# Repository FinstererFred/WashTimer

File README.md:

# WashTimer

Timer for washing machine. 

Features: 

- Set time when washing machine starts
- Activate / Deactivate timer
- Set clocktime via menu
- Reads active wash-program
- Display remaining washingtime for active wash-program

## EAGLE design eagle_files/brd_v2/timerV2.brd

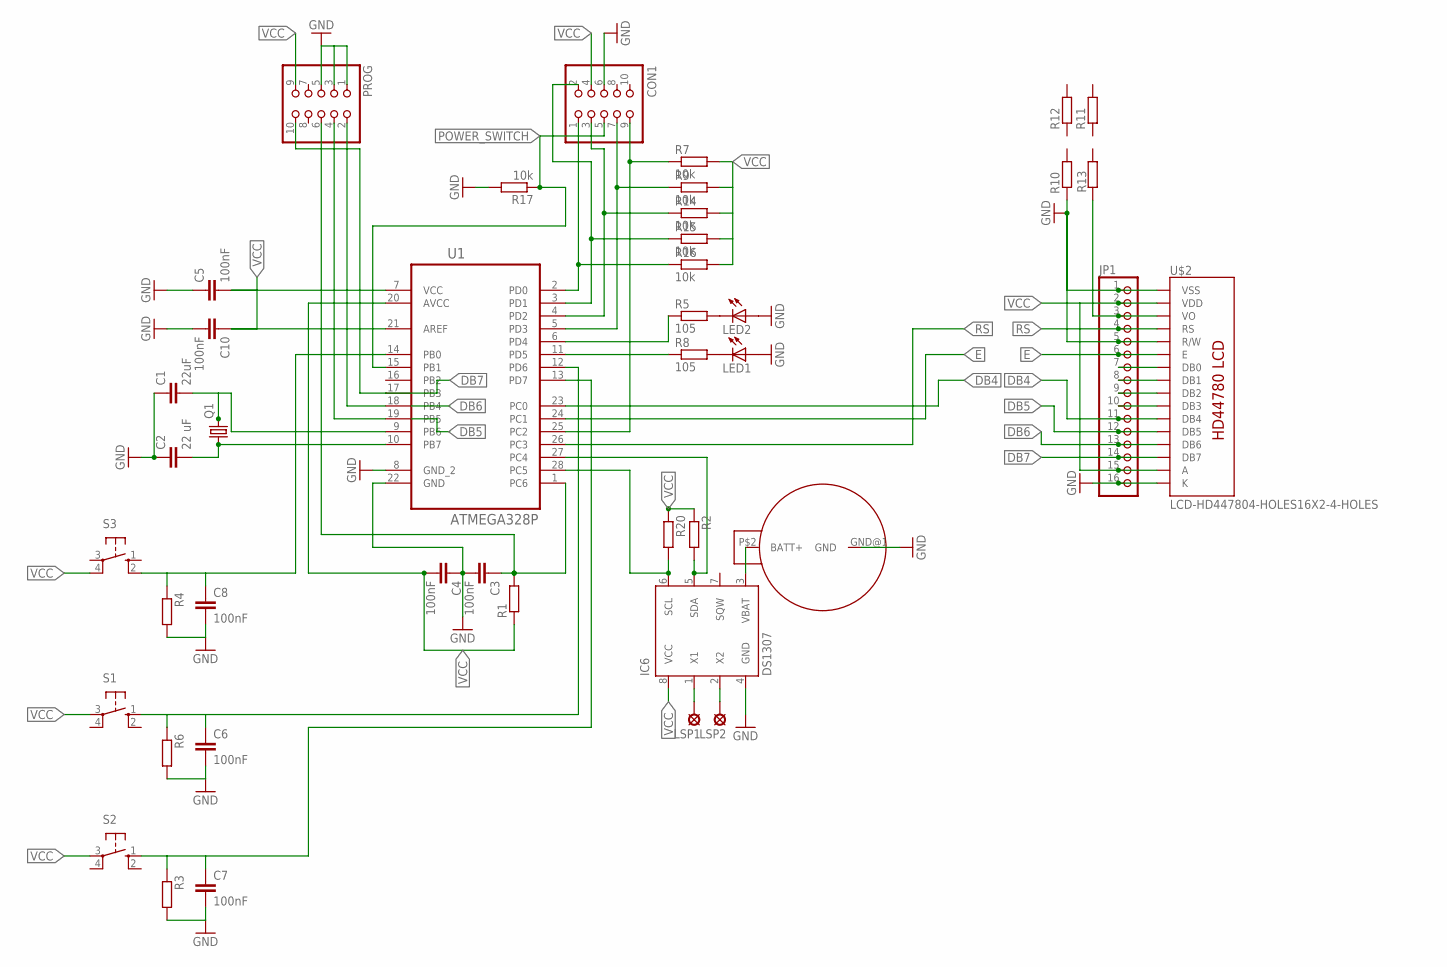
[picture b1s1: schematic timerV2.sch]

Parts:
C1: 22uF; C025-025X050
C2: 22 uF; C025-025X050
C3, C4, C5, C6, C7, C8, C10: 100nF; C0603
CON1: PINHD-2X5; 2X05
IC6: DS1307; DIL08
JP1: PINHD-1X16; 1X16
LED1, LED2: LED5MM
LSP1, LSP2: LSP10
PROG: PINHD-2X5; 2X05
Q1: CRYSTALHC49U-V; HC49U-V
R1, R2, R3, R4, R6, R10, R11, R12, R13, R20: RR0603; R0603
R5, R8: 105; R0603
R7, R9, R14, R15, R16, R17: 10k; R0603
S1, S2, S3: 10-XX; B3F-10XX
U1: ATMEGA328P; DIP254P762X457-28
U$1: CR2032; CR2023
U$2: LCD-HD447804-HOLES16X2-4-HOLES; LCD-16X2-4HOLES

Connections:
DB4: JP1.11, U1.23 (PC0), U$2.11 (DB4)
DB5: JP1.12, PROG.4, U1.19 (PB5), U$2.12 (DB5)
DB6: JP1.13, PROG.2, U1.18 (PB4), U$2.13 (DB6)
DB7: JP1.14, PROG.10, U1.17 (PB3), U$2.14 (DB7)
E: JP1.6, U1.24 (PC1), U$2.6 (E)
GND: C1.1, C2.1, C3.2, C4.1, C5.1, C6.2, C7.2, C8.2, C10.2, CON1.6, IC6.4 (GND), JP1.1, JP1.5, JP1.16, LED1.A, LED2.A, PROG.1, PROG.3, PROG.5, R3.2, R4.2, R6.2, R10.1, R17.2, U1.8 (GND_2), U1.22 (GND), U$1.GND@1 (GND), U$2.1 (VSS), U$2.5 (R/W), U$2.16 (K)
unnamed: LED2.K (C), R5.2
unnamed: JP1.3, R13.2, U$2.3 (VO)
unnamed: LED1.K (C), R8.2
unnamed: C3.1, PROG.6, R1.2, U1.1 (PC6)
unnamed: C7.1, R3.1, S2.1 (S), U1.13 (PD7)
unnamed: CON1.2, R15.1, U1.3 (PD1)
unnamed: JP1.7, U$2.7 (DB0)
unnamed: C8.1, R4.1, S3.2 (S1), U1.14 (PB0)
unnamed: CON1.7, R9.1, U1.5 (PD3)
unnamed: R8.1, U1.11 (PD5)
unnamed: R5.1, U1.6 (PD4)
unnamed: CON1.1, R16.1, U1.2 (PD0)
unnamed: JP1.8, U$2.8 (DB1)
unnamed: CON1.3, R14.1, U1.4 (PD2)
unnamed: JP1.9, U$2.9 (DB2)
unnamed: JP1.10, U$2.10 (DB3)
unnamed: C6.1, R6.1, S1.1 (S), U1.12 (PD6)
unnamed: IC6.2 (X2), LSP2.MP
unnamed: IC6.1 (X1), LSP1.MP
unnamed: IC6.3 (VBAT), U$1.P$2 (BATT+)
unnamed: IC6.6 (SCL), R20.2, U1.28 (PC5)
unnamed: IC6.5 (SDA), R2.2, U1.27 (PC4)
unnamed: C1.2, Q1.2, U1.9 (PB6)
unnamed: C2.2, Q1.1, U1.10 (PB7)
POWER_SWITCH: CON1.5, R17.1, U1.15 (PB1)
RS: JP1.4, U1.26 (PC3), U$2.4 (RS)
RW: CON1.9, R7.1, U1.25 (PC2)
VCC: C4.2, C5.2, C10.1, CON1.4, IC6.8 (VCC), JP1.2, JP1.15, PROG.9, R1.1, R2.1, R7.2, R9.2, R14.2, R15.2, R16.2, R20.1, S1.3, S2.3, S3.4 (P1), U1.7 (VCC), U1.20 (AVCC), U1.21 (AREF), U$2.2 (VDD), U$2.15 (A)

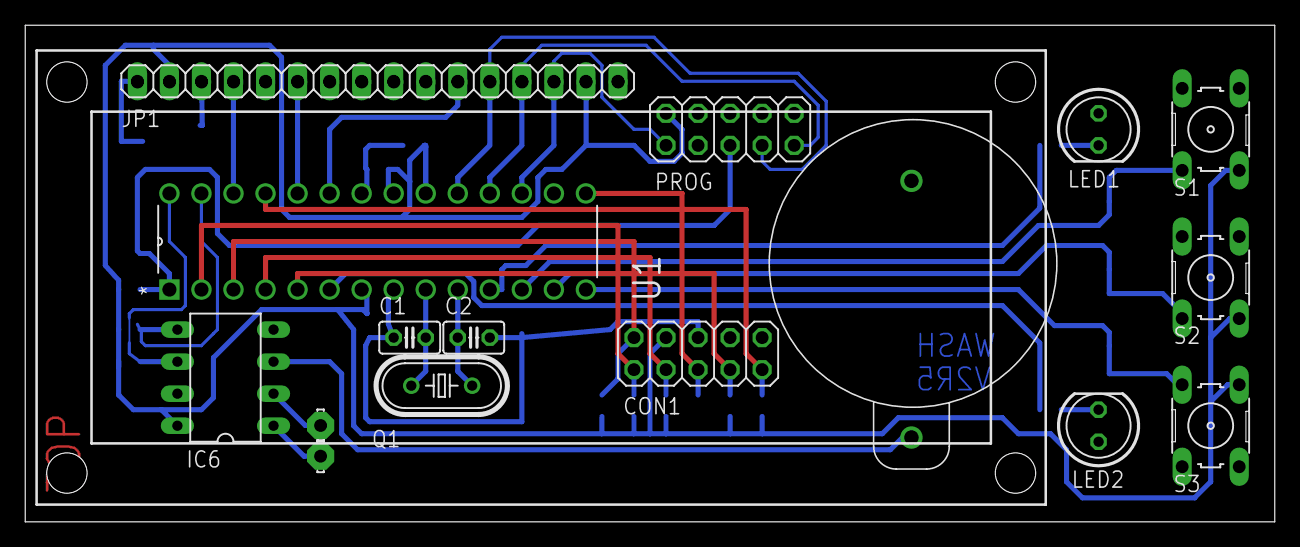
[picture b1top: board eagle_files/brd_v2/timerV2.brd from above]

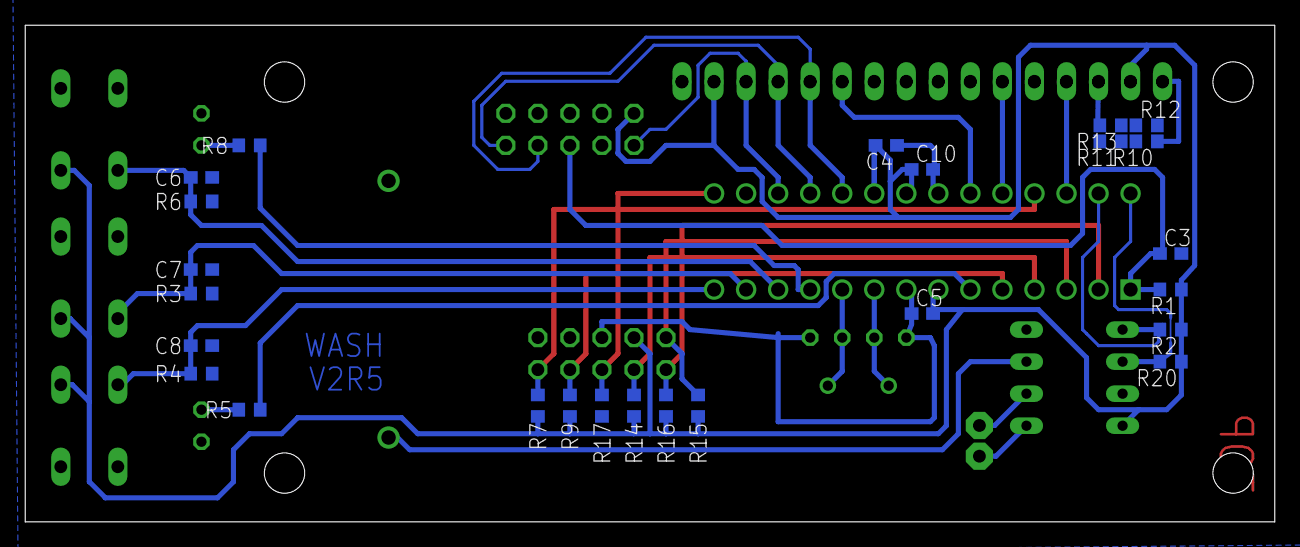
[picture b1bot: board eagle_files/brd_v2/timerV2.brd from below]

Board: 2 copper layers, 99.1 x 39.4 mm, 42 parts (25 on the bottom side), 34 nets.

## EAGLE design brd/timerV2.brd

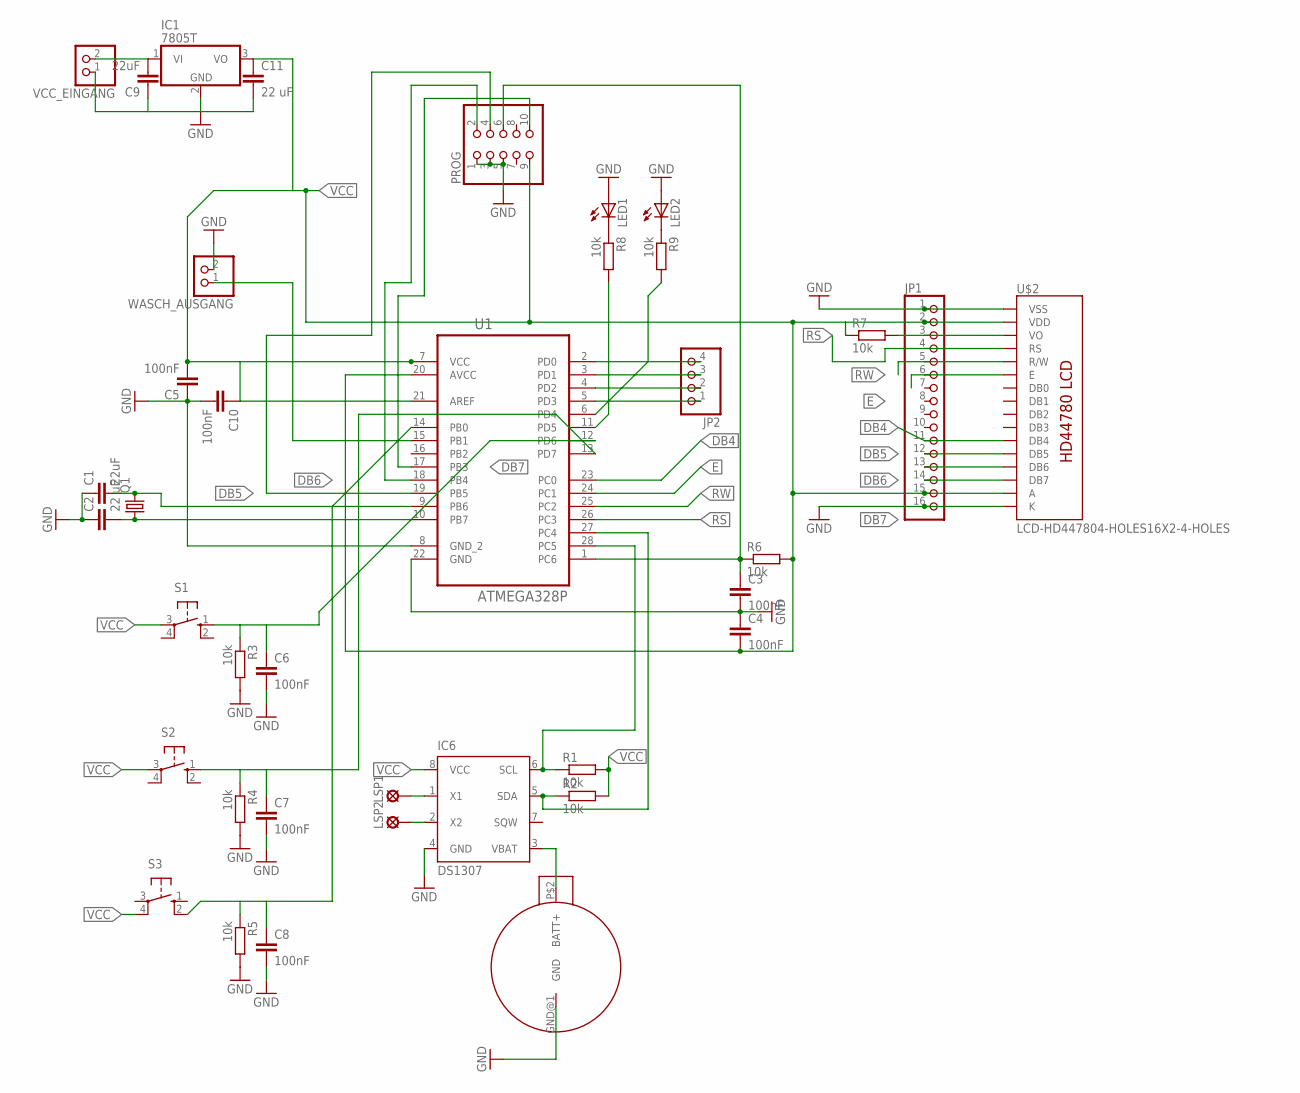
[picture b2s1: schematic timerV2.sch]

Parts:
C1, C9: 22uF; C025-025X050
C2, C11: 22 uF; C025-025X050
C3, C4, C5, C6, C7, C8, C10: 100nF; C0603
IC1: 7805T; TO220H
IC6: DS1307; DIL08
JP1: PINHD-1X16; 1X16
JP2: PINHD-1X4/90; 1X04/90
LED1, LED2: LED5MM
LSP1, LSP2: LSP10
PROG: PINHD-2X5; 2X05
Q1: CRYSTALHC49U-V; HC49U-V
R1, R2, R3, R4, R5, R6, R7, R8, R9: 10k; 0204/7
S1, S2, S3: 10-XX; B3F-10XX
U1: ATMEGA328P; DIP254P762X457-28
U$1: CR2032; CR2023
U$2: LCD-HD447804-HOLES16X2-4-HOLES; LCD-16X2-4HOLES
VCC_EINGANG: PINHD-1X2; 1X02
WASCH_AUSGANG: PINHD-1X2; 1X02

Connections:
DB4: JP1.11, U1.23 (PC0), U$2.11 (DB4)
DB5: JP1.12, PROG.4, U1.19 (PB5), U$2.12 (DB5)
DB6: JP1.13, PROG.2, U1.18 (PB4), U$2.13 (DB6)
DB7: JP1.14, PROG.10, U1.17 (PB3), U$2.14 (DB7)
E: JP1.6, U1.24 (PC1), U$2.6 (E)
GND: C1.1, C2.1, C3.2, C4.1, C5.1, C6.2, C7.2, C8.2, C9.1, C10.2, C11.2, IC1.2 (GND), IC6.4 (GND), JP1.1, JP1.16, LED1.A, LED2.A, PROG.1, PROG.3, PROG.5, R3.2, R4.2, R5.2, U1.8 (GND_2), U1.22 (GND), U$1.GND@1 (GND), U$2.1 (VSS), U$2.16 (K), VCC_EINGANG.1, WASCH_AUSGANG.2
unnamed: LED1.K (C), R8.1
unnamed: JP1.3, R7.2, U$2.3 (VO)
unnamed: U1.15 (PB1), WASCH_AUSGANG.1
unnamed: LED2.K (C), R9.1
unnamed: C3.1, PROG.6, R6.1, U1.1 (PC6)
unnamed: JP2.4, U1.2 (PD0)
unnamed: C9.2, IC1.1 (VI), VCC_EINGANG.2
unnamed: C7.1, R4.1, S2.1 (S), U1.13 (PD7)
unnamed: JP2.3, U1.3 (PD1)
unnamed: JP2.2, U1.4 (PD2)
unnamed: C8.1, R5.1, S3.2 (S1), U1.14 (PB0)
unnamed: JP2.1, U1.5 (PD3)
unnamed: R8.2, U1.11 (PD5)
unnamed: R9.2, U1.6 (PD4)
unnamed: C6.1, R3.1, S1.1 (S), U1.12 (PD6)
unnamed: IC6.2 (X2), LSP2.MP
unnamed: IC6.1 (X1), LSP1.MP
unnamed: IC6.3 (VBAT), U$1.P$2 (BATT+)
unnamed: IC6.6 (SCL), R1.1, U1.28 (PC5)
unnamed: IC6.5 (SDA), R2.1, U1.27 (PC4)
unnamed: C1.2, Q1.2, U1.9 (PB6)
unnamed: C2.2, Q1.1, U1.10 (PB7)
RS: JP1.4, U1.26 (PC3), U$2.4 (RS)
RW: JP1.5, U1.25 (PC2), U$2.5 (R/W)
VCC: C4.2, C5.2, C10.1, C11.1, IC1.3 (VO), IC6.8 (VCC), JP1.2, JP1.15, PROG.9, R1.2, R2.2, R6.2, R7.1, S1.3, S2.3, S3.4 (P1), U1.7 (VCC), U1.20 (AVCC), U1.21 (AREF), U$2.2 (VDD), U$2.15 (A)

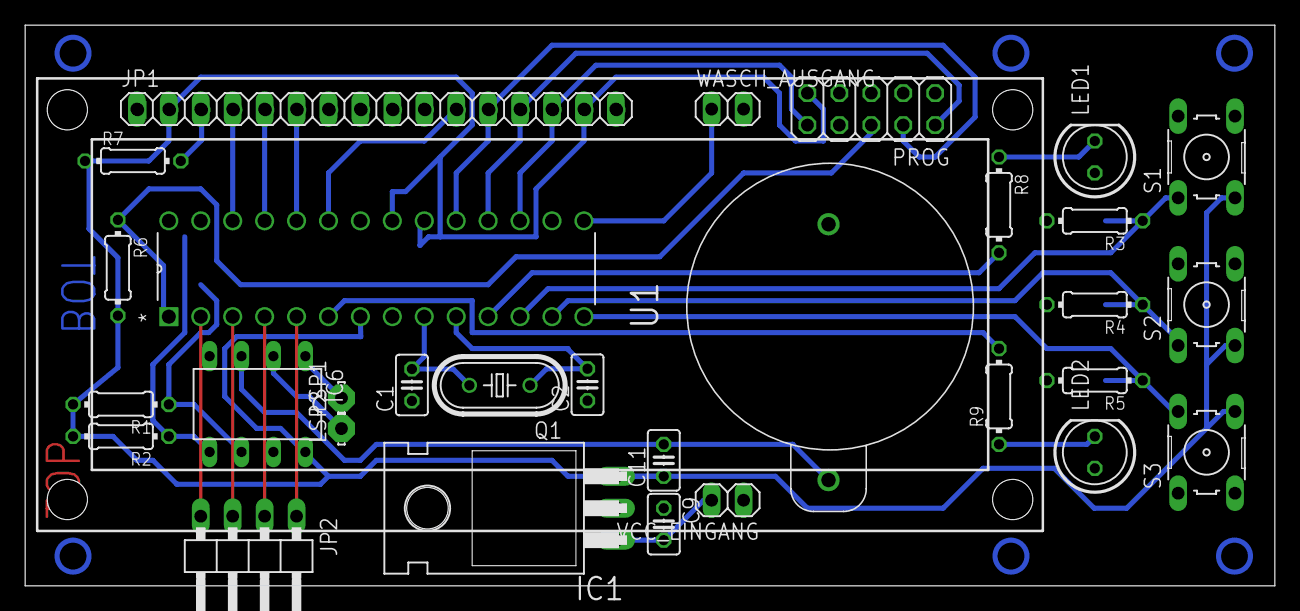
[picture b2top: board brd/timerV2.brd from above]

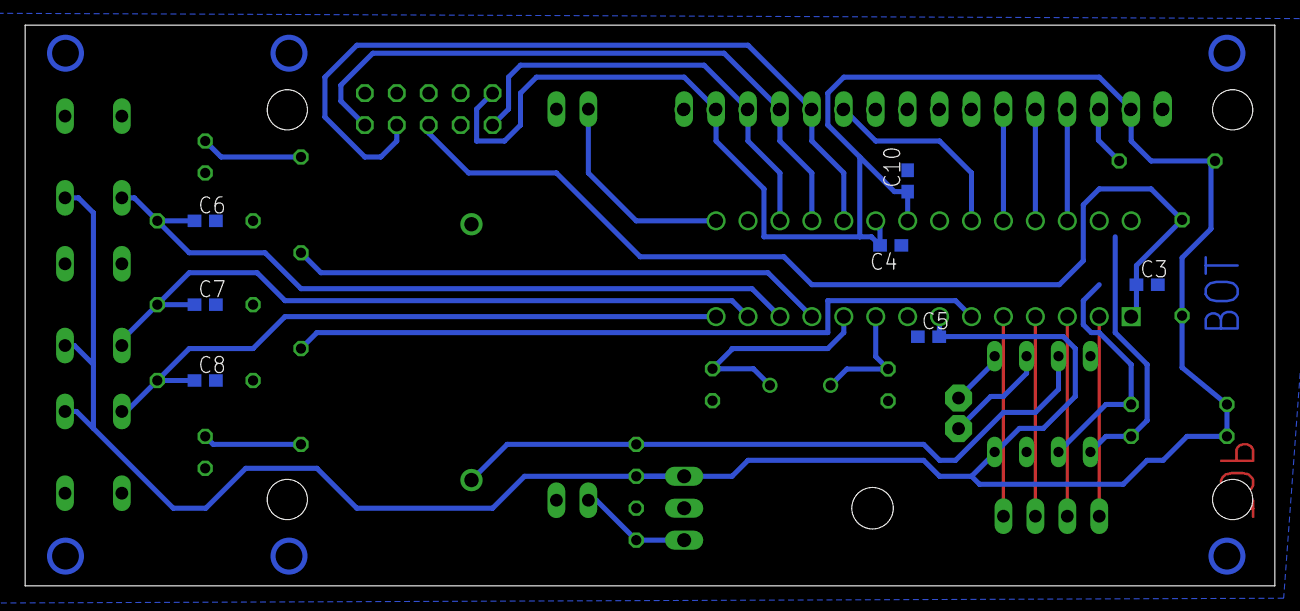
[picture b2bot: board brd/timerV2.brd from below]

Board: 2 copper layers, 99.4 x 44.6 mm, 38 parts (7 on the bottom side), 31 nets.

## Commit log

2015-08-20 Updated Board File, DS1307 Demo Code
2015-08-21 Updated Board and added DS1307 to Program
2015-08-21 Fixed Timer Stop check
2015-08-25 - Added Countdown of selected wash proogram - added states for running and active timer
2015-08-26 - Added Clock Set menu - Added External Pin interrupt Code - Restructured code
2015-08-28 - Added Blink - Fixed Seconds on Countdown
2015-09-01 renamed directory
2015-09-01 restructured eagle files
2015-09-01 deleted old code file
2015-09-02 added more input pins removed voltage regulator added pinheader
2015-09-02 Added Pulldown resistors for input pins
2015-09-02 changed board layout
2015-09-03 added pullup resistors ...
2015-09-03 changed layout
2015-09-04 Schematic cleaned up
